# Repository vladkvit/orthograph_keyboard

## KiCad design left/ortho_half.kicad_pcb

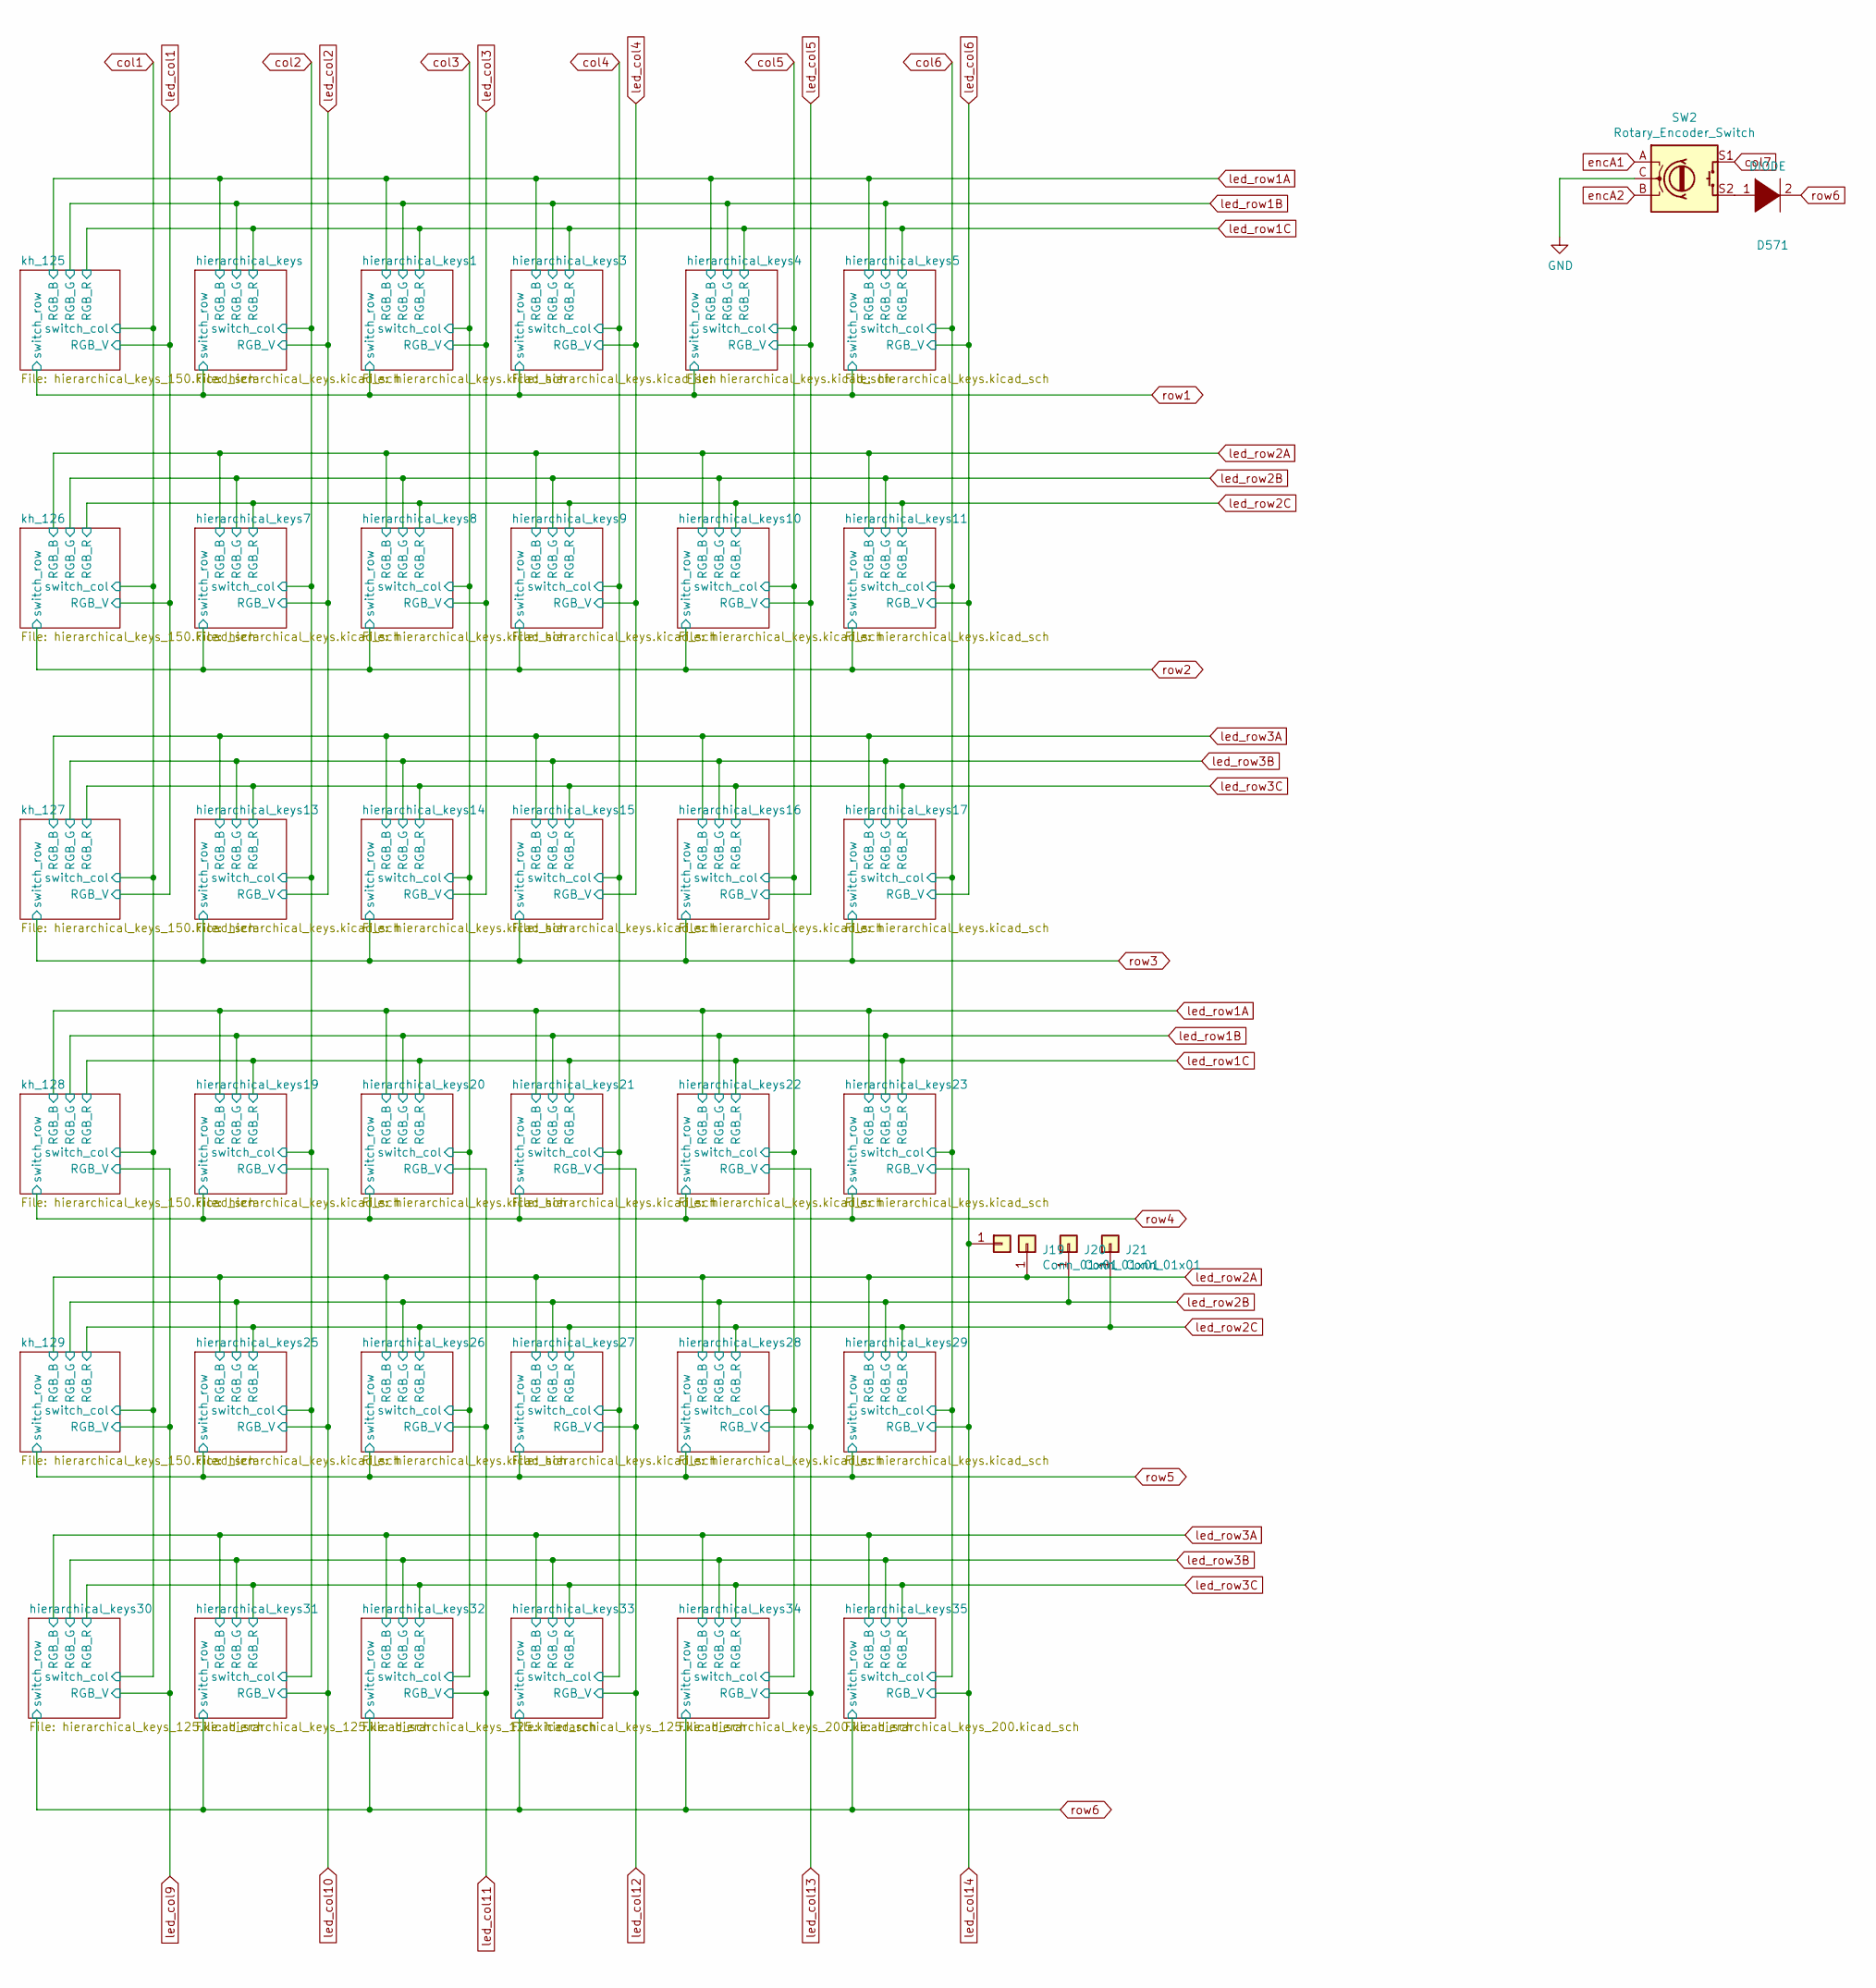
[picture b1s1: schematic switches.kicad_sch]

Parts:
D571: DIODE; D_SOD-123; LCSC C77978
J18, J19, J20, J21: Conn_01x01; TestPoint_Pad_D1.5mm
SW2: Rotary_Encoder_Switch; RotaryEncoderEC11_MX_combo; LCSC C470742

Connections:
GND: SW2.C; also elsewhere on the board
unnamed: D571.1 (K), SW2.S2
col7: SW2.S1; also elsewhere on the board
encA1: SW2.A; also elsewhere on the board
encA2: SW2.B; also elsewhere on the board
led_col14: J18.1; also elsewhere on the board
led_row2A: J19.1; also elsewhere on the board
led_row2B: J20.1; also elsewhere on the board
led_row2C: J21.1; also elsewhere on the board
row6: D571.2 (A); also elsewhere on the board

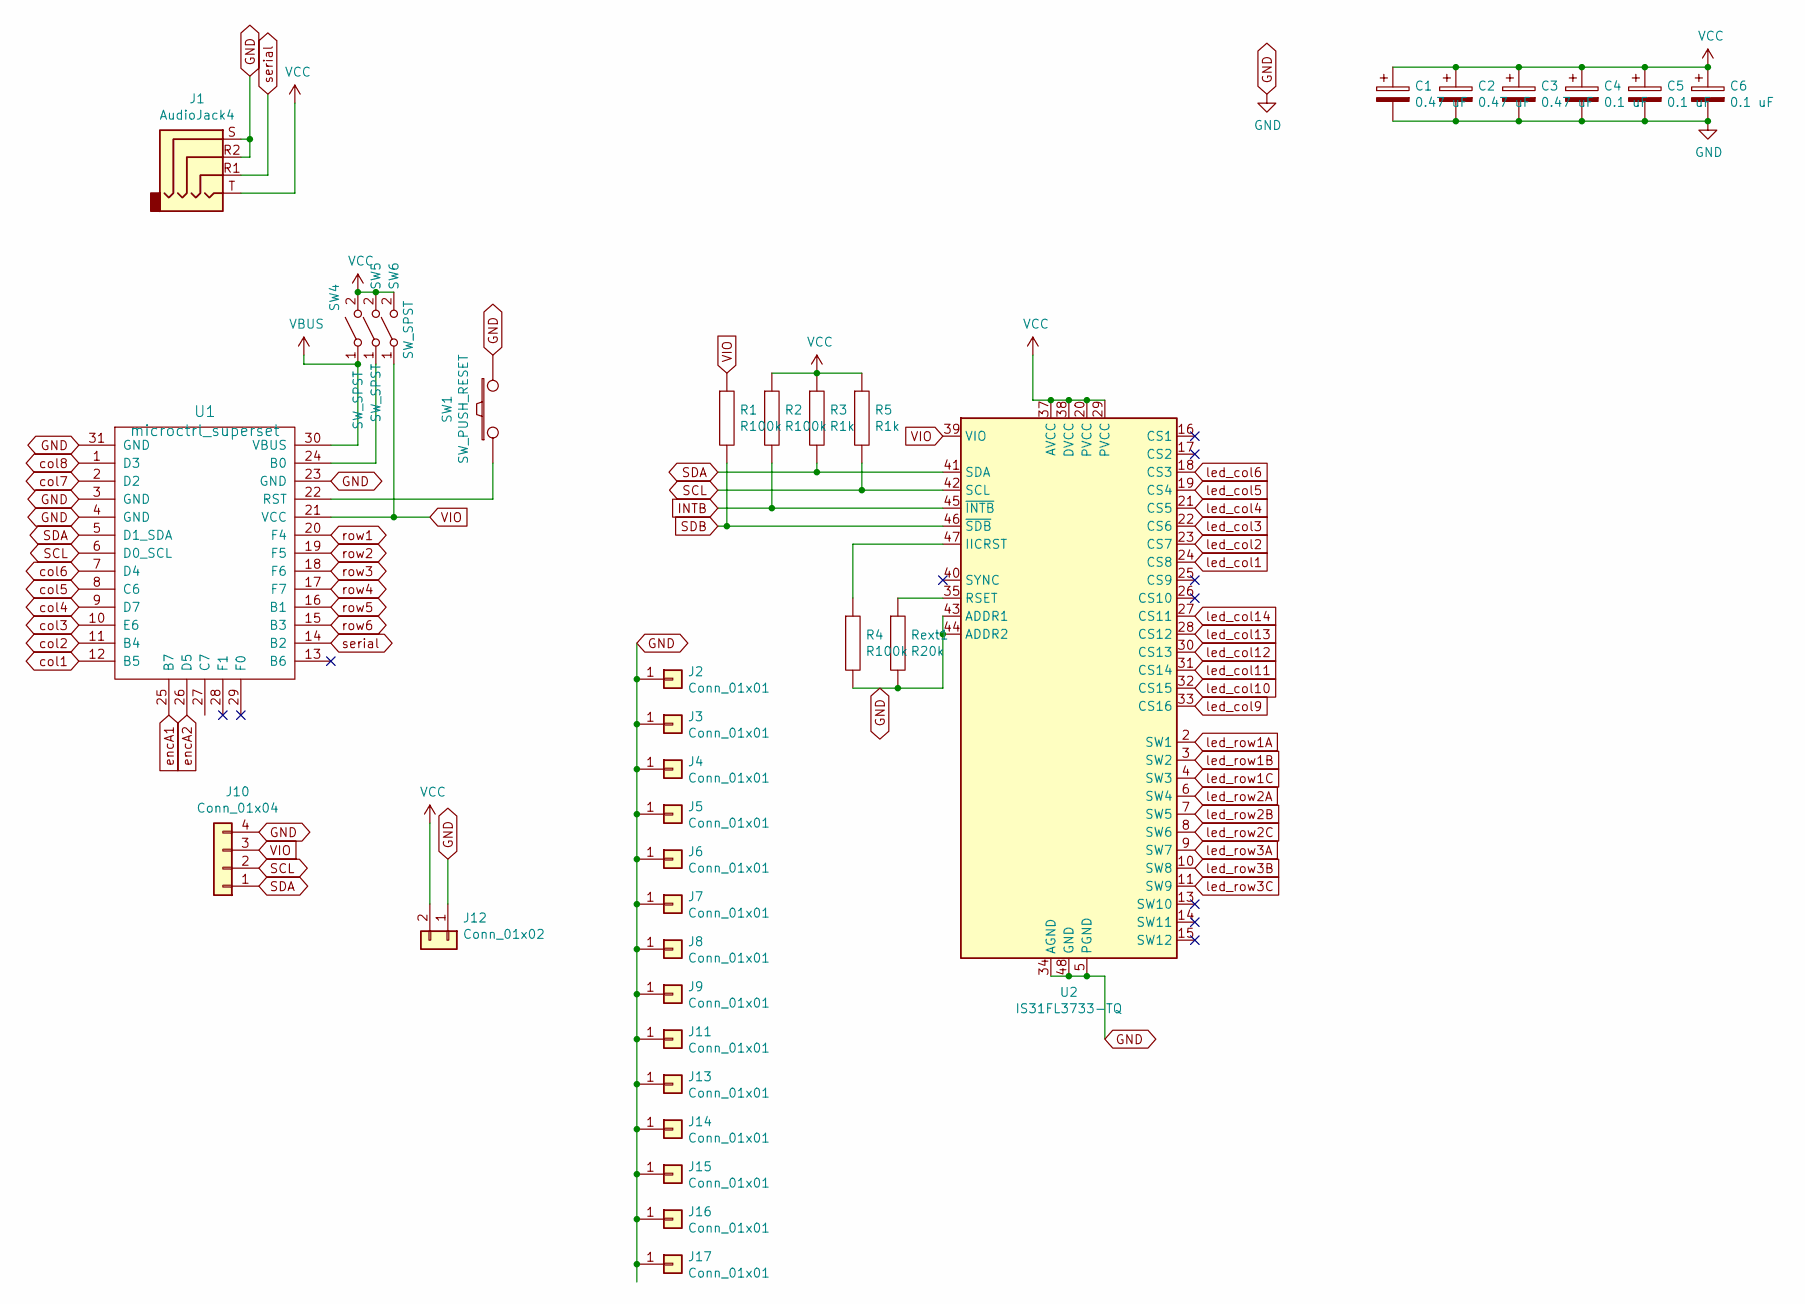
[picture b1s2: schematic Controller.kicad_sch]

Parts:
C1, C2, C3: 0.47 uF; C_0805_2012Metric; LCSC C49955
C4, C5, C6: 0.1 uF; C_0805_2012Metric; LCSC C49678
J1: AudioJack4; TRRS-PJ-320D; LCSC C431535
J2, J3, J5, J6, J7, J9, J11, J17: Conn_01x01; SMTSO_mount_m2.5; LCSC C2916379
J4, J8: Conn_01x01; m2.5_hole
J10: Conn_01x04; PinHeader_1x04_P2.54mm_Vertical
J12: Conn_01x02; battery_solder_point
J13, J14, J15, J16: Conn_01x01; standoff_m2.5
R1, R2, R4: R100k; R_0603_1608Metric; LCSC C25803
R3, R5: R1k; R_0603_1608Metric; LCSC C21190
Rext1: R20k; R_0603_1608Metric; LCSC C4184
SW1: SW_PUSH_RESET; SW_Push_1P1T_NO_CK_KMR2; LCSC C99271
SW4, SW5, SW6: SW_SPST; SolderJumper-2_P1.3mm_Open_RoundedPad1.0x1.5mm
U1: microctrl_superset; microcontroller_eliteC_ninenano
U2: IS31FL3733-TQ; TQFP-48-1EP_7x7mm_P0.5mm_EP5x5mm; LCSC C17348851

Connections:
GND: C1.2, C2.2, C3.2, C4.2, C5.2, C6.2, J1.R2, J1.S, J2.1, J3.1, J4.1, J5.1, J6.1, J7.1, J8.1, J9.1, J10.4, J11.1, J12.1, J13.1, J14.1, J15.1, J16.1, J17.1, R4.2, Rext1.2, SW1.2, U1.3 (GND), U1.4 (GND), U1.23 (GND), U1.31 (GND), U2.5 (PGND), U2.12 (PGND), U2.34 (AGND), U2.43 (ADDR1), U2.44 (ADDR2), U2.48 (GND), U2.49 (GND); also elsewhere on the board
INTB: R2.2, U2.45 (~INTB)
unnamed: SW5.1 (A), U1.24 (B0)
unnamed: SW1.1, U1.22 (RST)
unnamed: R4.1, U2.47 (IICRST)
unnamed: Rext1.1, U2.35 (RSET)
SCL: J10.2, R5.2, U1.6 (D0_SCL), U2.42 (SCL)
SDA: J10.1, R3.2, U1.5 (D1_SDA), U2.41 (SDA)
SDB: R1.2, U2.46 (~SDB)
VBUS: SW4.1 (A), U1.30 (VBUS)
VCC: C1.1, C2.1, C3.1, C4.1, C5.1, C6.1, J1.T, J12.2, R2.1, R3.1, R5.1, SW4.2 (B), SW5.2 (B), SW6.2 (B), U2.20 (PVCC), U2.29 (PVCC), U2.37 (AVCC), U2.38 (DVCC)
VIO: J10.3, R1.1, SW6.1 (A), U1.21 (VCC), U2.39 (VIO)
col1: U1.12 (B5); also elsewhere on the board
col2: U1.11 (B4); also elsewhere on the board
col3: U1.10 (E6); also elsewhere on the board
col4: U1.9 (D7); also elsewhere on the board
col5: U1.8 (C6); also elsewhere on the board
col6: U1.7 (D4); also elsewhere on the board
col7: U1.2 (D2); also elsewhere on the board
col8: U1.1 (D3)
encA1: U1.25 (B7); also elsewhere on the board
encA2: U1.26 (D5); also elsewhere on the board
led_col1: U2.24 (CS8); also elsewhere on the board
led_col2: U2.23 (CS7); also elsewhere on the board
led_col3: U2.22 (CS6); also elsewhere on the board
led_col4: U2.21 (CS5); also elsewhere on the board
led_col5: U2.19 (CS4); also elsewhere on the board
led_col6: U2.18 (CS3); also elsewhere on the board
led_col9: U2.33 (CS16); also elsewhere on the board
led_col10: U2.32 (CS15); also elsewhere on the board
led_col11: U2.31 (CS14); also elsewhere on the board
led_col12: U2.30 (CS13); also elsewhere on the board
led_col13: U2.28 (CS12); also elsewhere on the board
led_col14: U2.27 (CS11); also elsewhere on the board
led_row1A: U2.2 (SW1); also elsewhere on the board
led_row1B: U2.3 (SW2); also elsewhere on the board
led_row1C: U2.4 (SW3); also elsewhere on the board
led_row2A: U2.6 (SW4); also elsewhere on the board
led_row2B: U2.7 (SW5); also elsewhere on the board
led_row2C: U2.8 (SW6); also elsewhere on the board
led_row3A: U2.9 (SW7); also elsewhere on the board
led_row3B: U2.10 (SW8); also elsewhere on the board
led_row3C: U2.11 (SW9); also elsewhere on the board
row1: U1.20 (F4); also elsewhere on the board
row2: U1.19 (F5); also elsewhere on the board
row3: U1.18 (F6); also elsewhere on the board
row4: U1.17 (F7); also elsewhere on the board
row5: U1.16 (B1); also elsewhere on the board
row6: U1.15 (B3); also elsewhere on the board
serial: J1.R1, U1.14 (B2)

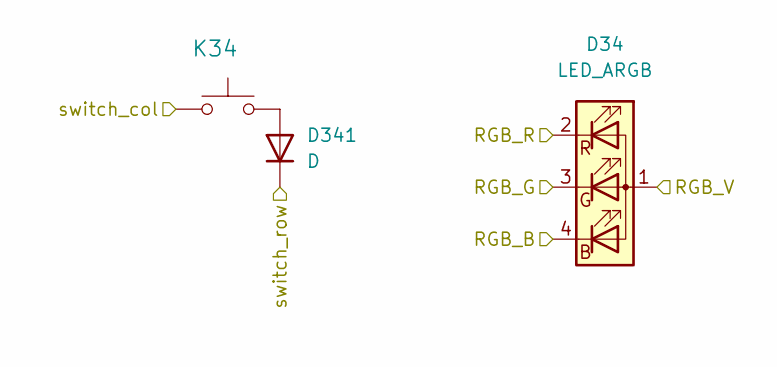
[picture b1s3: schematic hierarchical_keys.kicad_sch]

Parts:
D34: LED_ARGB; MX_RGB
D341: D; D_SOD-123
K34: KEYSW; MX_switch_hotswap

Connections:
unnamed: D341.2 (A), K34.2
col4: K34.1; also elsewhere on the board
led_col4: D34.1 (A); also elsewhere on the board
led_row3A: D34.4 (BK); also elsewhere on the board
led_row3B: D34.3 (GK); also elsewhere on the board
led_row3C: D34.2 (RK); also elsewhere on the board
row3: D341.1 (K); also elsewhere on the board

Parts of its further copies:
D12, D13, D14, D15, D16, D22, D23, D24, D25, D26, D32, D33, D35, D36, D42, D43, D44, D45, D46, D52, D53, D54, D55, D56, D61, D62, D63, D64, D65, D66: LED_ARGB; MX_RGB
D121, D131, D141, D151, D161, D221, D231, D241, D251, D261, D321, D331, D351, D361, D421, D431, D441, D451, D461, D521, D531, D541, D551, D561, D611, D621, D631, D641, D651, D661: D; D_SOD-123
K12, K13, K14, K15, K16, K22, K23, K24, K25, K26, K32, K33, K35, K36, K42, K43, K44, K45, K46, K52, K53, K54, K55, K56, K61, K62, K63, K64, K65, K66: KEYSW; MX_switch_hotswap

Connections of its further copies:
unnamed: D121.2 (A), K12.2
unnamed: D131.2 (A), K13.2
unnamed: D141.2 (A), K14.2
unnamed: D151.2 (A), K15.2
unnamed: D161.2 (A), K16.2
unnamed: D221.2 (A), K22.2
unnamed: D231.2 (A), K23.2
unnamed: D241.2 (A), K24.2
unnamed: D251.2 (A), K25.2
unnamed: D261.2 (A), K26.2
unnamed: D321.2 (A), K32.2
unnamed: D331.2 (A), K33.2
unnamed: D351.2 (A), K35.2
unnamed: D361.2 (A), K36.2
unnamed: D421.2 (A), K42.2
unnamed: D431.2 (A), K43.2
unnamed: D441.2 (A), K44.2
unnamed: D451.2 (A), K45.2
unnamed: D461.2 (A), K46.2
unnamed: D521.2 (A), K52.2
unnamed: D531.2 (A), K53.2
unnamed: D541.2 (A), K54.2
unnamed: D551.2 (A), K55.2
unnamed: D561.2 (A), K56.2
unnamed: D611.2 (A), K61.2
unnamed: D621.2 (A), K62.2
unnamed: D631.2 (A), K63.2
unnamed: D641.2 (A), K64.2
unnamed: D651.2 (A), K65.2
unnamed: D661.2 (A), K66.2
col1: K61.1; also elsewhere on the board
col2: K12.1, K22.1, K32.1, K42.1, K52.1, K62.1; also elsewhere on the board
col3: K13.1, K23.1, K33.1, K43.1, K53.1, K63.1; also elsewhere on the board
col4: K14.1, K24.1, K44.1, K54.1, K64.1; also elsewhere on the board
col5: K15.1, K25.1, K35.1, K45.1, K55.1, K65.1; also elsewhere on the board
col6: K16.1, K26.1, K36.1, K46.1, K56.1, K66.1; also elsewhere on the board
led_col2: D12.1 (A), D22.1 (A), D32.1 (A); also elsewhere on the board
led_col3: D13.1 (A), D23.1 (A), D33.1 (A); also elsewhere on the board
led_col4: D14.1 (A), D24.1 (A); also elsewhere on the board
led_col5: D15.1 (A), D25.1 (A), D35.1 (A); also elsewhere on the board
led_col6: D16.1 (A), D26.1 (A), D36.1 (A); also elsewhere on the board
led_col9: D61.1 (A); also elsewhere on the board
led_col10: D42.1 (A), D52.1 (A), D62.1 (A); also elsewhere on the board
led_col11: D43.1 (A), D53.1 (A), D63.1 (A); also elsewhere on the board
led_col12: D44.1 (A), D54.1 (A), D64.1 (A); also elsewhere on the board
led_col13: D45.1 (A), D55.1 (A), D65.1 (A); also elsewhere on the board
led_col14: D46.1 (A), D56.1 (A), D66.1 (A); also elsewhere on the board
led_row1A: D12.4 (BK), D13.4 (BK), D14.4 (BK), D15.4 (BK), D16.4 (BK), D42.4 (BK), D43.4 (BK), D44.4 (BK), D45.4 (BK), D46.4 (BK); also elsewhere on the board
led_row1B: D12.3 (GK), D13.3 (GK), D14.3 (GK), D15.3 (GK), D16.3 (GK), D42.3 (GK), D43.3 (GK), D44.3 (GK), D45.3 (GK), D46.3 (GK); also elsewhere on the board
led_row1C: D12.2 (RK), D13.2 (RK), D14.2 (RK), D15.2 (RK), D16.2 (RK), D42.2 (RK), D43.2 (RK), D44.2 (RK), D45.2 (RK), D46.2 (RK); also elsewhere on the board
led_row2A: D22.4 (BK), D23.4 (BK), D24.4 (BK), D25.4 (BK), D26.4 (BK), D52.4 (BK), D53.4 (BK), D54.4 (BK), D55.4 (BK), D56.4 (BK); also elsewhere on the board
led_row2B: D22.3 (GK), D23.3 (GK), D24.3 (GK), D25.3 (GK), D26.3 (GK), D52.3 (GK), D53.3 (GK), D54.3 (GK), D55.3 (GK), D56.3 (GK); also elsewhere on the board
led_row2C: D22.2 (RK), D23.2 (RK), D24.2 (RK), D25.2 (RK), D26.2 (RK), D52.2 (RK), D53.2 (RK), D54.2 (RK), D55.2 (RK), D56.2 (RK); also elsewhere on the board
led_row3A: D32.4 (BK), D33.4 (BK), D35.4 (BK), D36.4 (BK), D61.4 (BK), D62.4 (BK), D63.4 (BK), D64.4 (BK), D65.4 (BK), D66.4 (BK); also elsewhere on the board
led_row3B: D32.3 (GK), D33.3 (GK), D35.3 (GK), D36.3 (GK), D61.3 (GK), D62.3 (GK), D63.3 (GK), D64.3 (GK), D65.3 (GK), D66.3 (GK); also elsewhere on the board
led_row3C: D32.2 (RK), D33.2 (RK), D35.2 (RK), D36.2 (RK), D61.2 (RK), D62.2 (RK), D63.2 (RK), D64.2 (RK), D65.2 (RK), D66.2 (RK); also elsewhere on the board
row1: D121.1 (K), D131.1 (K), D141.1 (K), D151.1 (K), D161.1 (K); also elsewhere on the board
row2: D221.1 (K), D231.1 (K), D241.1 (K), D251.1 (K), D261.1 (K); also elsewhere on the board
row3: D321.1 (K), D331.1 (K), D351.1 (K), D361.1 (K); also elsewhere on the board
row4: D421.1 (K), D431.1 (K), D441.1 (K), D451.1 (K), D461.1 (K); also elsewhere on the board
row5: D521.1 (K), D531.1 (K), D541.1 (K), D551.1 (K), D561.1 (K); also elsewhere on the board
row6: D611.1 (K), D621.1 (K), D631.1 (K), D641.1 (K), D651.1 (K), D661.1 (K); also elsewhere on the board

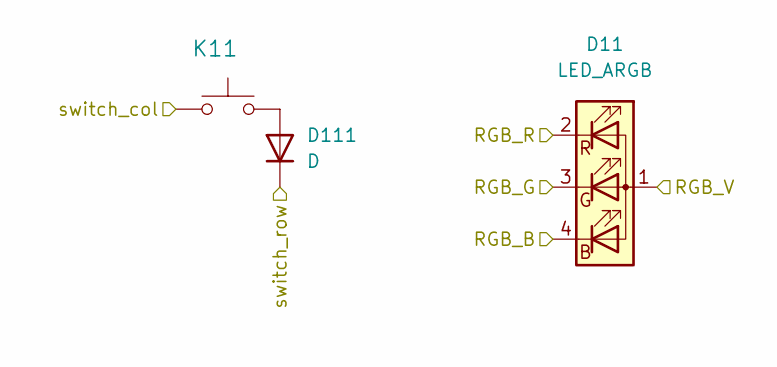
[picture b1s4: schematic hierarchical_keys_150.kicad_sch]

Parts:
D11: LED_ARGB; MX_RGB
D111: D; D_SOD-123
K11: KEYSW; MX_switch_hotswap_150

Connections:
unnamed: D111.2 (A), K11.2
col1: K11.1; also elsewhere on the board
led_col1: D11.1 (A); also elsewhere on the board
led_row1A: D11.4 (BK); also elsewhere on the board
led_row1B: D11.3 (GK); also elsewhere on the board
led_row1C: D11.2 (RK); also elsewhere on the board
row1: D111.1 (K); also elsewhere on the board

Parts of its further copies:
D21, D41, D51: LED_ARGB; MX_RGB
D211, D411, D511: D; D_SOD-123
K21, K41, K51: KEYSW; MX_switch_hotswap_150

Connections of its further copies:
unnamed: D211.2 (A), K21.2
unnamed: D411.2 (A), K41.2
unnamed: D511.2 (A), K51.2
col1: K21.1, K41.1, K51.1; also elsewhere on the board
led_col1: D21.1 (A); also elsewhere on the board
led_col9: D41.1 (A), D51.1 (A); also elsewhere on the board
led_row1A: D41.4 (BK); also elsewhere on the board
led_row1B: D41.3 (GK); also elsewhere on the board
led_row1C: D41.2 (RK); also elsewhere on the board
led_row2A: D21.4 (BK), D51.4 (BK); also elsewhere on the board
led_row2B: D21.3 (GK), D51.3 (GK); also elsewhere on the board
led_row2C: D21.2 (RK), D51.2 (RK); also elsewhere on the board
row2: D211.1 (K); also elsewhere on the board
row4: D411.1 (K); also elsewhere on the board
row5: D511.1 (K); also elsewhere on the board

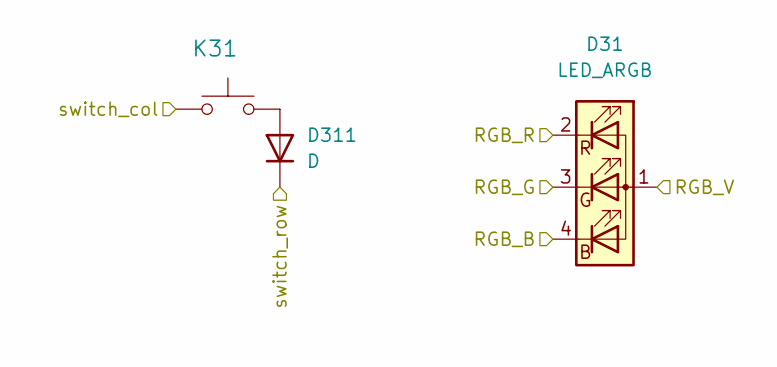
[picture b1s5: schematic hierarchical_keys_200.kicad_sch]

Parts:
D31: LED_ARGB; MX_RGB
D311: D; D_SOD-123
K31: KEYSW; MX_switch_hotswap_200

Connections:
unnamed: D311.2 (A), K31.2
col1: K31.1; also elsewhere on the board
led_col1: D31.1 (A); also elsewhere on the board
led_row3A: D31.4 (BK); also elsewhere on the board
led_row3B: D31.3 (GK); also elsewhere on the board
led_row3C: D31.2 (RK); also elsewhere on the board
row3: D311.1 (K); also elsewhere on the board

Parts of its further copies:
D21, D41, D51, D65, D66: LED_ARGB; MX_RGB
D211, D411, D511, D651, D661: D; D_SOD-123
K21, K41, K51, K65, K66: KEYSW; MX_switch_hotswap_200

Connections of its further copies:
unnamed: D211.2 (A), K21.2
unnamed: D411.2 (A), K41.2
unnamed: D511.2 (A), K51.2
unnamed: D651.2 (A), K65.2
unnamed: D661.2 (A), K66.2
col1: K21.1, K41.1, K51.1; also elsewhere on the board
col5: K65.1; also elsewhere on the board
col6: K66.1; also elsewhere on the board
led_col1: D21.1 (A); also elsewhere on the board
led_col9: D41.1 (A), D51.1 (A); also elsewhere on the board
led_col13: D65.1 (A); also elsewhere on the board
led_col14: D66.1 (A); also elsewhere on the board
led_row1A: D41.4 (BK); also elsewhere on the board
led_row1B: D41.3 (GK); also elsewhere on the board
led_row1C: D41.2 (RK); also elsewhere on the board
led_row2A: D21.4 (BK), D51.4 (BK); also elsewhere on the board
led_row2B: D21.3 (GK), D51.3 (GK); also elsewhere on the board
led_row2C: D21.2 (RK), D51.2 (RK); also elsewhere on the board
led_row3A: D65.4 (BK), D66.4 (BK); also elsewhere on the board
led_row3B: D65.3 (GK), D66.3 (GK); also elsewhere on the board
led_row3C: D65.2 (RK), D66.2 (RK); also elsewhere on the board
row2: D211.1 (K); also elsewhere on the board
row4: D411.1 (K); also elsewhere on the board
row5: D511.1 (K); also elsewhere on the board
row6: D651.1 (K), D661.1 (K); also elsewhere on the board

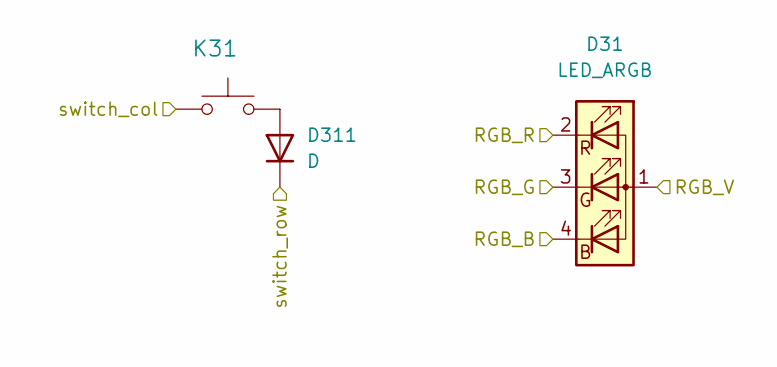
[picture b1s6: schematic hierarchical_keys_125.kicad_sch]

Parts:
D31: LED_ARGB; MX_RGB
D311: D; D_SOD-123
K31: KEYSW; MX_switch_hotswap_125

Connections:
unnamed: D311.2 (A), K31.2
col1: K31.1; also elsewhere on the board
led_col1: D31.1 (A); also elsewhere on the board
led_row3A: D31.4 (BK); also elsewhere on the board
led_row3B: D31.3 (GK); also elsewhere on the board
led_row3C: D31.2 (RK); also elsewhere on the board
row3: D311.1 (K); also elsewhere on the board

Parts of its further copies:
D21, D41, D51, D61, D62, D63, D64: LED_ARGB; MX_RGB
D211, D411, D511, D611, D621, D631, D641: D; D_SOD-123
K21, K41, K51, K61, K62, K63, K64: KEYSW; MX_switch_hotswap_125

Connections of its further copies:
unnamed: D211.2 (A), K21.2
unnamed: D411.2 (A), K41.2
unnamed: D511.2 (A), K51.2
unnamed: D611.2 (A), K61.2
unnamed: D621.2 (A), K62.2
unnamed: D631.2 (A), K63.2
unnamed: D641.2 (A), K64.2
col1: K21.1, K41.1, K51.1, K61.1; also elsewhere on the board
col2: K62.1; also elsewhere on the board
col3: K63.1; also elsewhere on the board
col4: K64.1; also elsewhere on the board
led_col1: D21.1 (A); also elsewhere on the board
led_col9: D41.1 (A), D51.1 (A), D61.1 (A); also elsewhere on the board
led_col10: D62.1 (A); also elsewhere on the board
led_col11: D63.1 (A); also elsewhere on the board
led_col12: D64.1 (A); also elsewhere on the board
led_row1A: D41.4 (BK); also elsewhere on the board
led_row1B: D41.3 (GK); also elsewhere on the board
led_row1C: D41.2 (RK); also elsewhere on the board
led_row2A: D21.4 (BK), D51.4 (BK); also elsewhere on the board
led_row2B: D21.3 (GK), D51.3 (GK); also elsewhere on the board
led_row2C: D21.2 (RK), D51.2 (RK); also elsewhere on the board
led_row3A: D61.4 (BK), D62.4 (BK), D63.4 (BK), D64.4 (BK); also elsewhere on the board
led_row3B: D61.3 (GK), D62.3 (GK), D63.3 (GK), D64.3 (GK); also elsewhere on the board
led_row3C: D61.2 (RK), D62.2 (RK), D63.2 (RK), D64.2 (RK); also elsewhere on the board
row2: D211.1 (K); also elsewhere on the board
row4: D411.1 (K); also elsewhere on the board
row5: D511.1 (K); also elsewhere on the board
row6: D611.1 (K), D621.1 (K), D631.1 (K), D641.1 (K); also elsewhere on the board

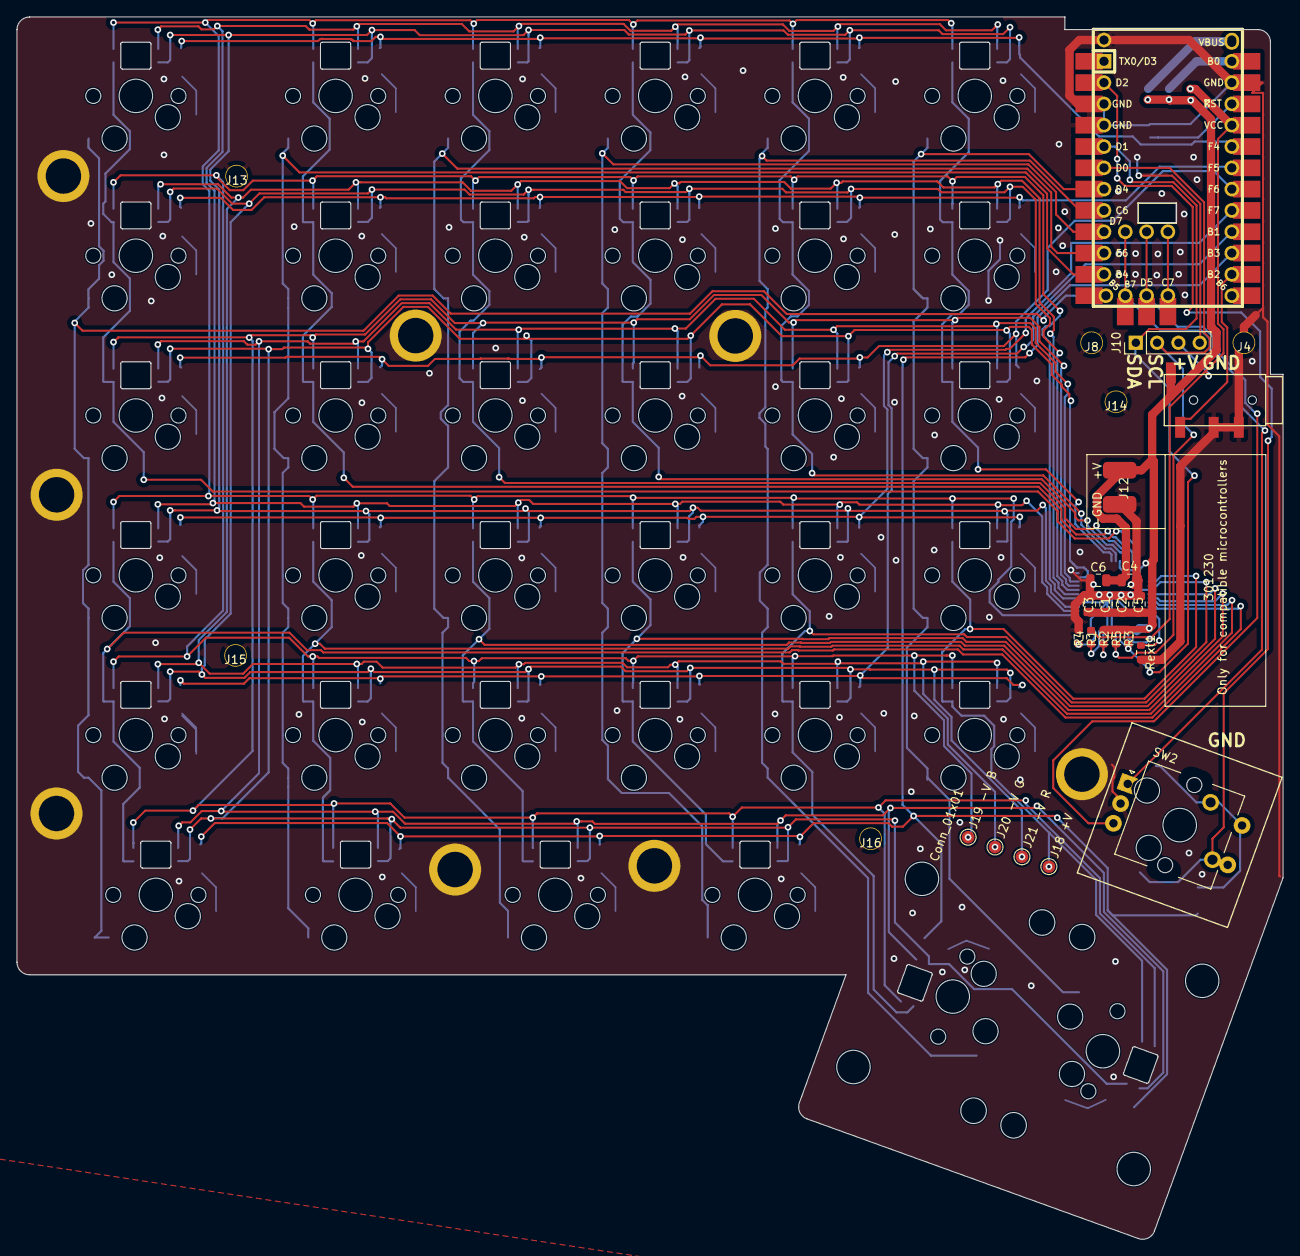
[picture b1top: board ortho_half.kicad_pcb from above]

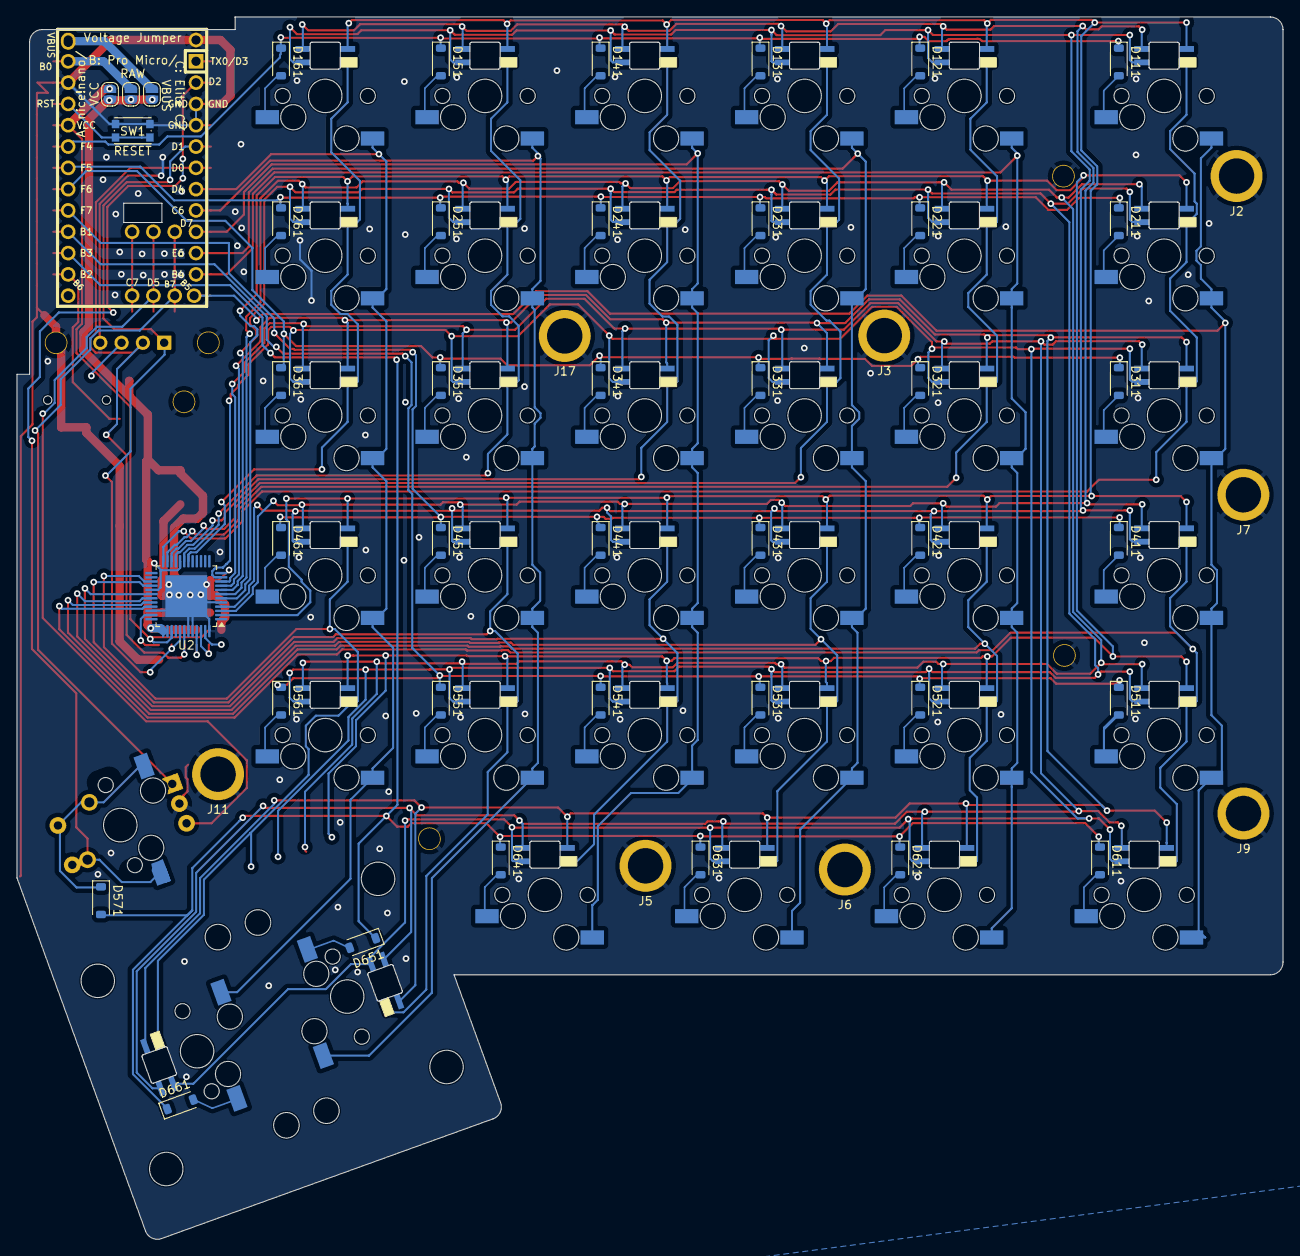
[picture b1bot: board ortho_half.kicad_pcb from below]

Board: 2 copper layers, 150.9 x 145.7 mm, 149 parts (50 on the bottom side), 86 nets.
